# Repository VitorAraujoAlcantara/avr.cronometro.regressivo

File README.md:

avr.cronometro.regressivo
=========================

Cronômetro regressivo utilizando atmega328, para ativar cargas via relé durante determinado tempo programado

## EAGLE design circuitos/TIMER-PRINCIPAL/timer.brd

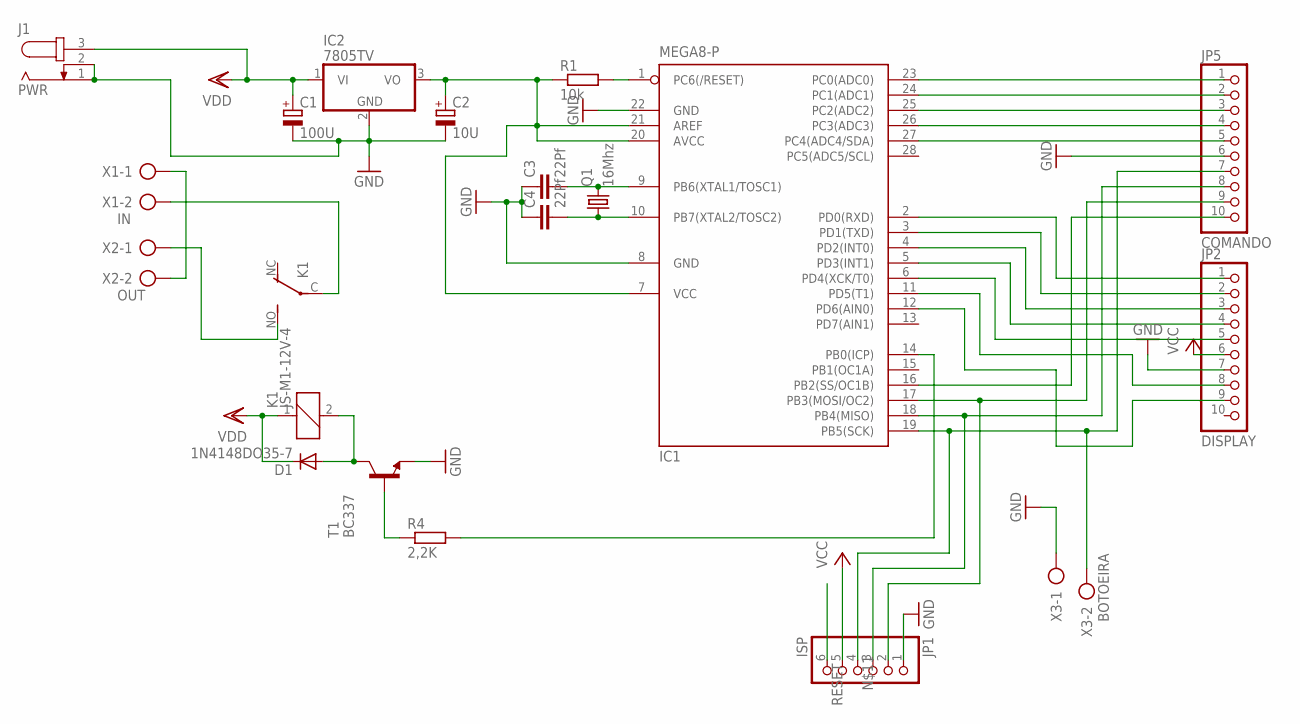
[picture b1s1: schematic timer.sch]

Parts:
C1: 100U; E2,5-6
C2: 10U; E2,5-6
C3, C4: 22Pf; C025-025X050
D1: 1N4148DO35-7; DO35-7
IC1: MEGA8-P; DIL28-3
IC2: 7805TV; TO220V
J1: PWR; SPC4078
JP1: ISP; 1X06
JP2: DISPLAY; 1X10
JP5: COMANDO; 1X10
K1: JS-M1-12V-4; JS-M
Q1: 16Mhz; HC49/S
R1: 10k; 0204/7
R4: 2,2K; 0204/7
T1: BC337; TO92
X1: IN; AK500/2
X2: OUT; AK500/2
X3: BOTOEIRA; AK500/2

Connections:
GND: C1.-, C2.-, C3.1, C4.1, IC1.8 (GND), IC1.22 (GND), IC2.2 (GND), J1.1, J1.2, JP1.1, JP2.7, JP5.6, T1.1 (E), X3.1
unnamed: X1.1, X2.2
unnamed: K1.NO (S), X2.1
unnamed: K1.C, X1.2
unnamed: C3.2, IC1.9 (PB6(XTAL1/TOSC1)), Q1.2
unnamed: C4.2, IC1.10 (PB7(XTAL2/TOSC2)), Q1.1
unnamed: IC1.23 (PC0(ADC0)), JP5.1
unnamed: IC1.24 (PC1(ADC1)), JP5.2
unnamed: IC1.25 (PC2(ADC2)), JP5.3
unnamed: IC1.26 (PC3(ADC3)), JP5.4
unnamed: IC1.27 (PC4(ADC4/SDA)), JP5.5
unnamed: IC1.19 (PB5(SCK)), JP1.4, JP5.7, X3.2
unnamed: IC1.16 (PB2(SS/OC1B)), JP5.10
unnamed: IC1.2 (PD0(RXD)), JP2.1
unnamed: IC1.3 (PD1(TXD)), JP2.2
unnamed: IC1.4 (PD2(INT0)), JP2.3
unnamed: IC1.5 (PD3(INT1)), JP2.4
unnamed: D1.A, K1.2, T1.3 (C)
unnamed: R4.1, T1.2 (B)
unnamed: IC1.14 (PB0(ICP)), R4.2
unnamed: IC1.18 (PB4(MISO)), JP1.3, JP5.8
unnamed: IC1.6 (PD4(XCK/T0)), JP2.5
unnamed: IC1.11 (PD5(T1)), JP2.8
unnamed: IC1.12 (PD6(AIN0)), JP2.9
unnamed: IC1.17 (PB3(MOSI/OC2)), JP1.2, JP5.9
RESET: IC1.1 (PC6(/RESET)), JP1.6, R1.2
VCC: C2.+, IC1.7 (VCC), IC1.20 (AVCC), IC1.21 (AREF), IC2.3 (VO), JP1.5, JP2.6, R1.1
VDD: C1.+, D1.C, IC2.1 (VI), J1.3, K1.1

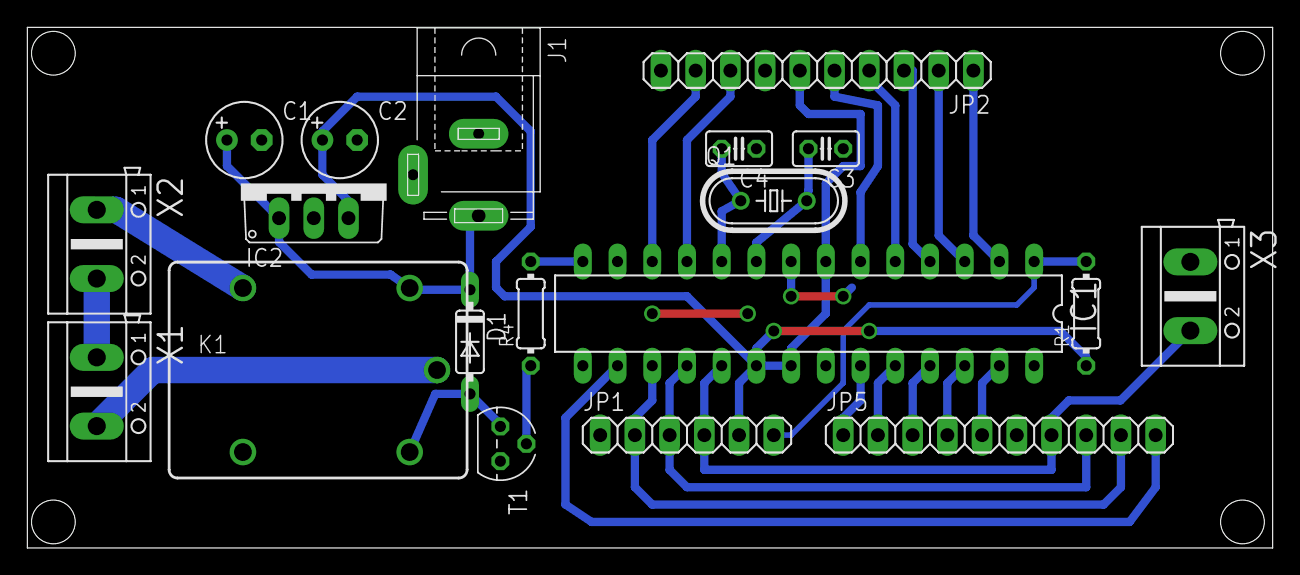
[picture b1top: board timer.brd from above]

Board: 2 copper layers, 91.1 x 38.1 mm, 19 parts (0 on the bottom side), 28 nets.

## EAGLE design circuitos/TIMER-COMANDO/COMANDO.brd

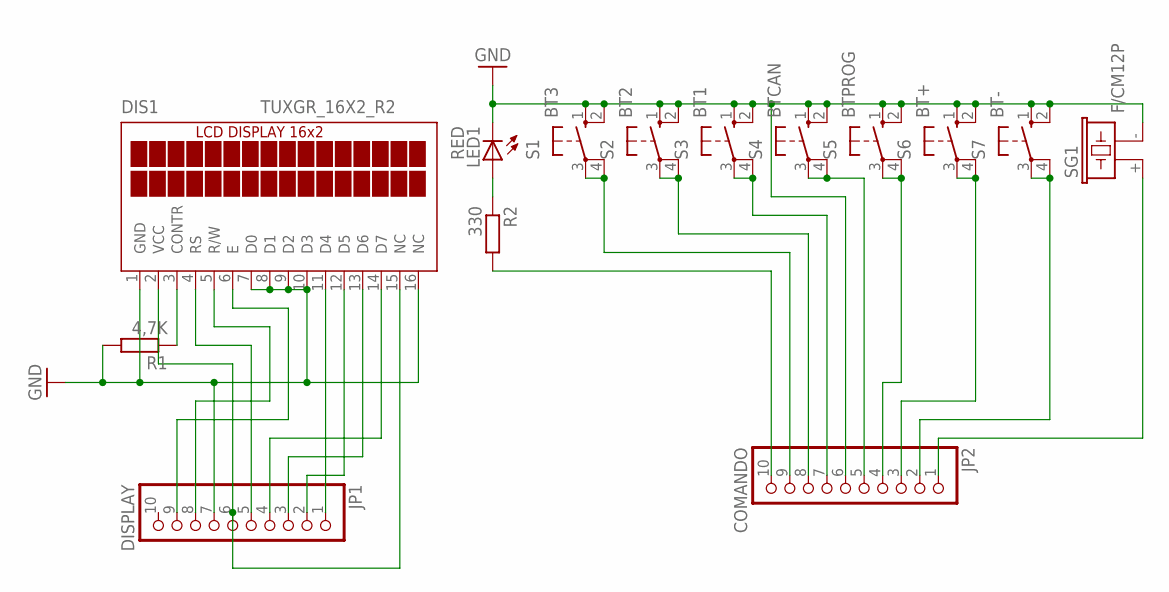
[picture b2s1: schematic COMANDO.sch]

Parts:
DIS1: TUXGR_16X2_R2
JP1: DISPLAY; 1X10
JP2: COMANDO; 1X10
LED1: RED; LED3MM
R1: 4,7K; 0207/10
R2: 330; 0207/10
S1: BT3; B3F-10XX
S2: BT2; B3F-10XX
S3: BT1; B3F-10XX
S4: BTCAN; B3F-10XX
S5: BTPROG; B3F-10XX
S6: BT+; B3F-10XX
S7: BT-; B3F-10XX
SG1: F/CM12P

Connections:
GND: DIS1.1 (GND), DIS1.7 (D0), DIS1.8 (D1), DIS1.9 (D2), DIS1.10 (D3), DIS1.16 (NC), JP1.7, JP2.6, LED1.K (C), R1.2, S1.1 (S), S1.2 (S1), S2.1 (S), S2.2 (S1), S3.1 (S), S3.2 (S1), S4.1 (S), S4.2 (S1), S5.1 (S), S5.2 (S1), S6.1 (S), S6.2 (S1), S7.1 (S), S7.2 (S1), SG1.- (2)
unnamed: DIS1.11 (D4), JP1.1
unnamed: DIS1.12 (D5), JP1.2
unnamed: DIS1.13 (D6), JP1.3
unnamed: DIS1.14 (D7), JP1.4
unnamed: DIS1.2 (VCC), DIS1.15 (NC), JP1.6
unnamed: DIS1.3 (CONTR), R1.1
unnamed: DIS1.4 (RS), JP1.5
unnamed: DIS1.5 (R/W), JP1.8
unnamed: DIS1.6 (E), JP1.9
unnamed: JP2.1, SG1.+ (1)
unnamed: JP2.2, S7.3, S7.4 (P1)
unnamed: JP2.3, S6.3, S6.4 (P1)
unnamed: JP2.4, S5.3, S5.4 (P1)
unnamed: JP2.5, S4.3, S4.4 (P1)
unnamed: JP2.7, S3.3, S3.4 (P1)
unnamed: JP2.8, S2.3, S2.4 (P1)
unnamed: JP2.9, S1.3, S1.4 (P1)
unnamed: LED1.A, R2.1
unnamed: JP2.10, R2.2

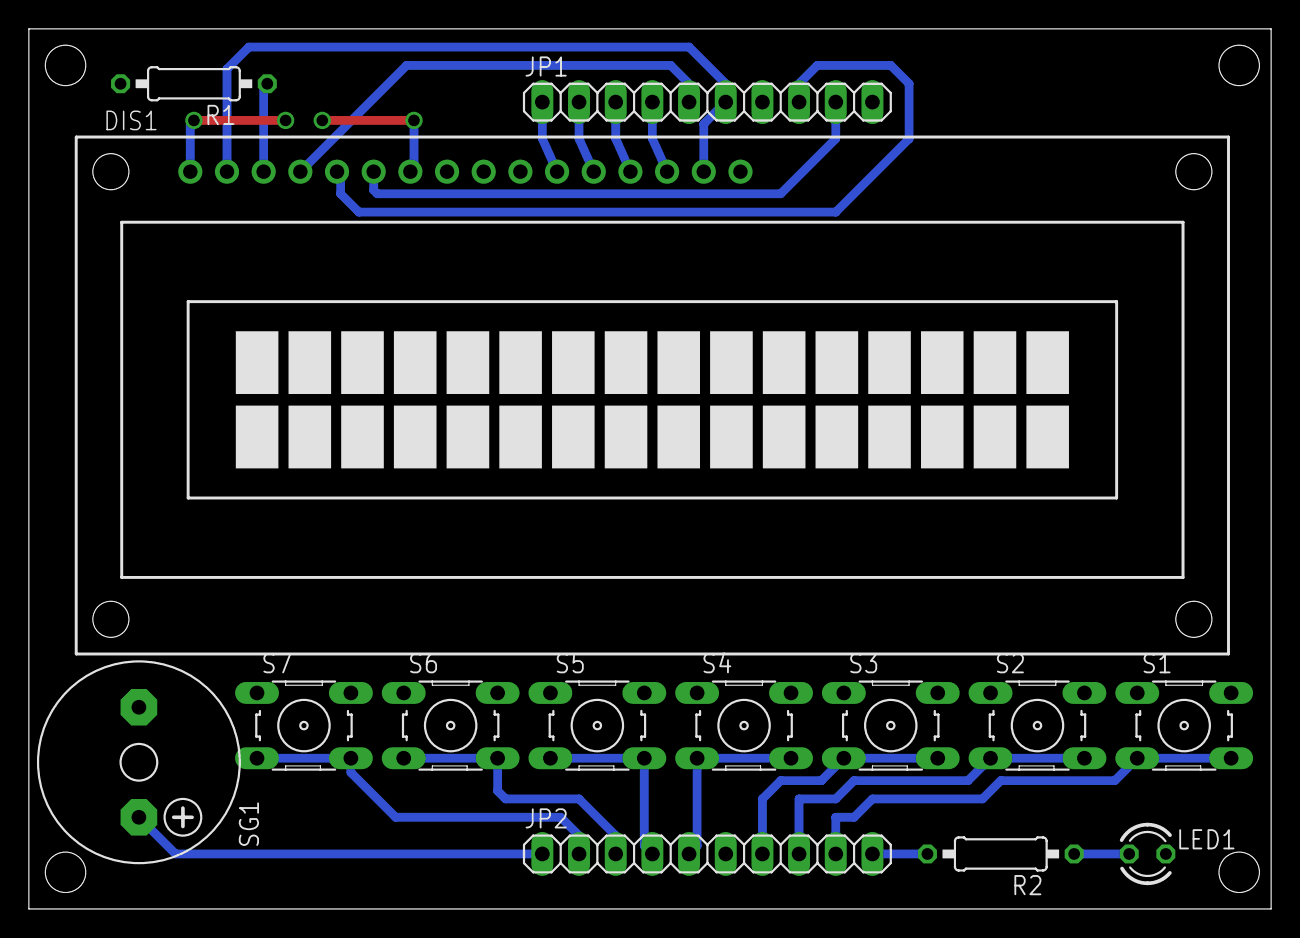
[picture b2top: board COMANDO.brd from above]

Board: 2 copper layers, 86.0 x 61.0 mm, 14 parts (0 on the bottom side), 20 nets.

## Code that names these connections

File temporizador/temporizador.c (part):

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
#define PORT_LED PORTB
#define DDR_LED DDRB
#define PINO_LED PB2

#define PORT_RELE PORTB
#define DDR_RELE DDRB
#define PINO_RELE PB0

#define PORT_BT1 PORTB
#define DDR_BT1 DDRB
#define PIN_BT1 PINB
#define PINO_BT1  PB5

#define PORT_BT2 PORTB
#define DDR_BT2 DDRB
#define PIN_BT2 PINB
#define PINO_BT2  PB4

#define PORT_BT3 PORTB
#define DDR_BT3 DDRB
#define PIN_BT3 PINB
#define PINO_BT3  PB3

#define PORT_CANCELA PORTC
#define DDR_CANCELA DDRC
#define PIN_CANCELA PINC
#define PINO_CANCELA  PC4

#define PORT_PROG PORTC
#define DDR_PROG DDRC
#define PIN_PROG PINC
#define PINO_PROG  PC3

#define PORT_MAIS PORTC
#define DDR_MAIS DDRC
#define PIN_MAIS PINC
#define PINO_MAIS  PC2

#define PORT_MENOS PORTC
#define DDR_MENOS DDRC
#define PIN_MENOS PINC
#define PINO_MENOS  PC1

#define PORT_BUZINA PORTC
#define DDR_BUZINA DDRC
#define PIN_BUZINA PINC
#define PINO_BUZINA PC0

static uint8_t enderecos[3][5] = { { 1, 2, 3, 4, 5 }, { 6, 7, 8, 9, 10 }, { 11,
		12, 13, 14, 15 } };
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
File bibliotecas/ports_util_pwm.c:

#include "ports_util.h"
static uint8_t ocr0a = 0;
static uint8_t ocr0b = 0;
static uint8_t ocr1a = 0;
static uint8_t ocr1b = 0;
static uint8_t ocr2a = 0;
static uint8_t ocr2b = 0;


void pwm_OCR0_disable()
{
	TCCR0A = 0x00;
	TCCR0B = 0x00;
	
}
void pwm_OCR1_disable()
{	
	TCCR1A = 0x00;
	TCCR1B = 0x00;	
}
void pwm_OCR2_disable()
{
	TCCR2A = 0x00;
	TCCR2B = 0x00;	
}

void pwm_OCR1_init (uint8_t _OCR1A, uint8_t _OCR1B) // PINOS 15 E 16
{
	ocr1a = _OCR1A;
	ocr1b = _OCR1B;
	if ( ocr1a )
	{
		on(DDRB,PB1);
		off(PORTB,PB1);
	}
	if ( ocr2b )
	{
		on(DDRB,PB2);	
		off(PORTB,PB2)	;
	}
	OCR1A = 0;
	OCR1B = 0;	

	TCCR1A |= (_OCR1A << COM1A1)|(_OCR1B << COM1B1);	
	TCCR1A |= (1 << WGM10);
	TCCR1B |= (1 << WGM12);	
	TCCR1B |= _BV(CS12) ;
}
void pwm_OCR0_init (  uint8_t  _OCR0A, uint8_t _OCR0B )  // PINOS 12 E 11
{
		OCR0A = 0;
		OCR0B = 0;
		
		ocr0a = _OCR0A;
		ocr0b = _OCR0B;
		
		if ( ocr0a )
		{
			on(DDRD,PD6);
			off(PORTD,PD6);
		}
		
		if ( ocr0b )
		{
			on(DDRD,PD5);
			off(PORTD,PD5);
		}
		
		TCCR0A =     _OCR0A <<  COM0A1 |    /* not inverted */
		0 << COM0A0 |
		_OCR0B << COM0B1 |    /* not inverted */
		0 << COM0B0 |
		1 << WGM01  |    /* fast pwm */
		1 << WGM00  ;    /* fast pwm */

		TCCR0B = 0 << FOC0A |
		0 << FOC0B |
		0 << WGM02 |     /* fast pwm */
		1 << CS02  |     /* div 256 prescale */
		0 << CS01  |
		0 << CS00  ;
}
void pwm_OCR2_init ( uint8_t _OCR2A, uint8_t _OCR2B)//PINOS 5 E 17
{
		ocr2a = _OCR2A;
		ocr2b = _OCR2B;
		if (ocr2a)
		{
			on(DDRB,PB3);
			off(PORTB,PB3);
		}
		
		if (ocr2b)
		{
			on(DDRD,PD3);
			off(PORTD,PD3);
		}
		OCR2A = 0;	
		OCR2B = 0;
		TCCR2A |= (_OCR2A << COM2A1)|(_OCR2B << COM2B1);
		TCCR2A |= (1 << WGM20);
		TCCR2A |= (1 << WGM21);
		TCCR2B |= _BV(CS22) | _BV(CS21) ;
}

void pwm_OCR0( uint8_t _OCR0A, uint8_t _OCR0B )
{		
	if (ocr0a )
	OCR0A = _OCR0A;
	if (ocr0b)
	OCR0B = _OCR0B;
}
void pwm_OCR1( uint8_t _OCR1A, uint8_t _OCR1B)
{
	if (ocr1a)
		OCR1A = _OCR1A;
	if (ocr1b)
		OCR1B = _OCR1B;	
}
void pwm_OCR2( uint8_t _OCR2A, uint8_t _OCR2B)
{
	if (ocr2a)
	OCR2A = _OCR2A;
	if (ocr2b)
	OCR2B = _OCR2B;	
}

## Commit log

2013-08-14 SIMPLES TESTE
2013-08-14 inicio do projeto
2013-08-14 INCLUSÃO DE CIRCUITO
2013-08-15 Trocado o componente do relé
